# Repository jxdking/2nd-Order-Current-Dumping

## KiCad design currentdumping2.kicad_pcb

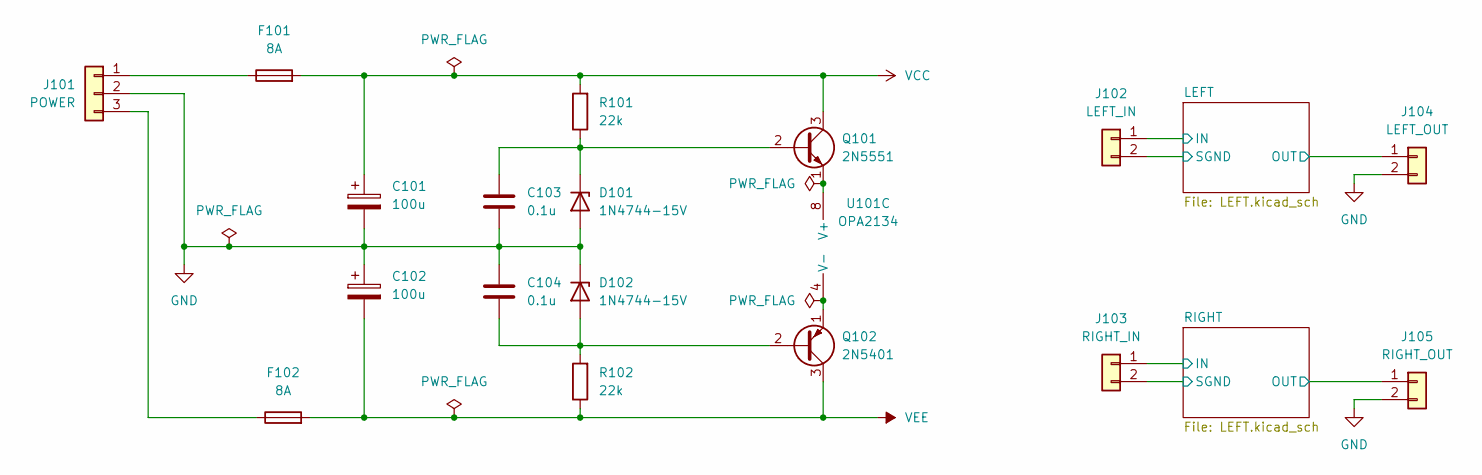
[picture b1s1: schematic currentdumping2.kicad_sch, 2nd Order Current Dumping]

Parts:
C101, C102: 100u; CP_Radial_D10.0mm_P5.00mm
C103, C104: 0.1u; C_Disc_D4.7mm_W2.5mm_P5.00mm
D101, D102: 1N4744-15V; D_DO-41_SOD81_P10.16mm_Horizontal
F101, F102: 8A; Fuseholder_Clip-5x20mm_Littelfuse_521_Lateral_P17.00x5.00mm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
J101: POWER; TerminalBlock_MaiXu_MX126-5.0-03P_1x03_P5.00mm
J102: LEFT_IN; TerminalBlock_MaiXu_MX126-5.0-02P_1x02_P5.00mm
J103: RIGHT_IN; TerminalBlock_MaiXu_MX126-5.0-02P_1x02_P5.00mm
J104: LEFT_OUT; TerminalBlock_MaiXu_MX126-5.0-02P_1x02_P5.00mm
J105: RIGHT_OUT; TerminalBlock_MaiXu_MX126-5.0-02P_1x02_P5.00mm
Q101: 2N5551; TO-92_Inline_Wide
Q102: 2N5401; TO-92_Inline_Wide
R101, R102: 22k; R_Axial_DIN0207_L6.3mm_D2.5mm_P10.16mm_Horizontal
U101: OPA2134; DIP-8_W7.62mm_Socket

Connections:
/LEFT/IN: J102.1; also elsewhere on the board
/LEFT/OUT: J104.1; also elsewhere on the board
/LEFT/SGND: J102.2; also elsewhere on the board
/RIGHT/IN: J103.1; also elsewhere on the board
/RIGHT/OUT: J105.1; also elsewhere on the board
/RIGHT/SGND: J103.2; also elsewhere on the board
GND: C101.2, C102.1, C103.2, C104.1, D101.2 (A), D102.1 (K), J101.2, J104.2, J105.2; also elsewhere on the board
unnamed: C103.1, D101.1 (K), Q101.2 (B), R101.1
unnamed: C104.2, D102.2 (A), Q102.2 (B), R102.2
unnamed: F101.1, J101.1
unnamed: F102.1, J101.3
unnamed: Q101.1 (E), U101.8 (V+)
unnamed: Q102.1 (E), U101.4 (V-)
unnamed 60: U101.7; also elsewhere on the board
unnamed 63: U101.5 (+); also elsewhere on the board
unnamed 64: U101.6 (-); also elsewhere on the board
VCC: C101.1, F101.2, Q101.3 (C), R101.2; also elsewhere on the board
VEE: C102.2, F102.2, Q102.3 (C), R102.1; also elsewhere on the board

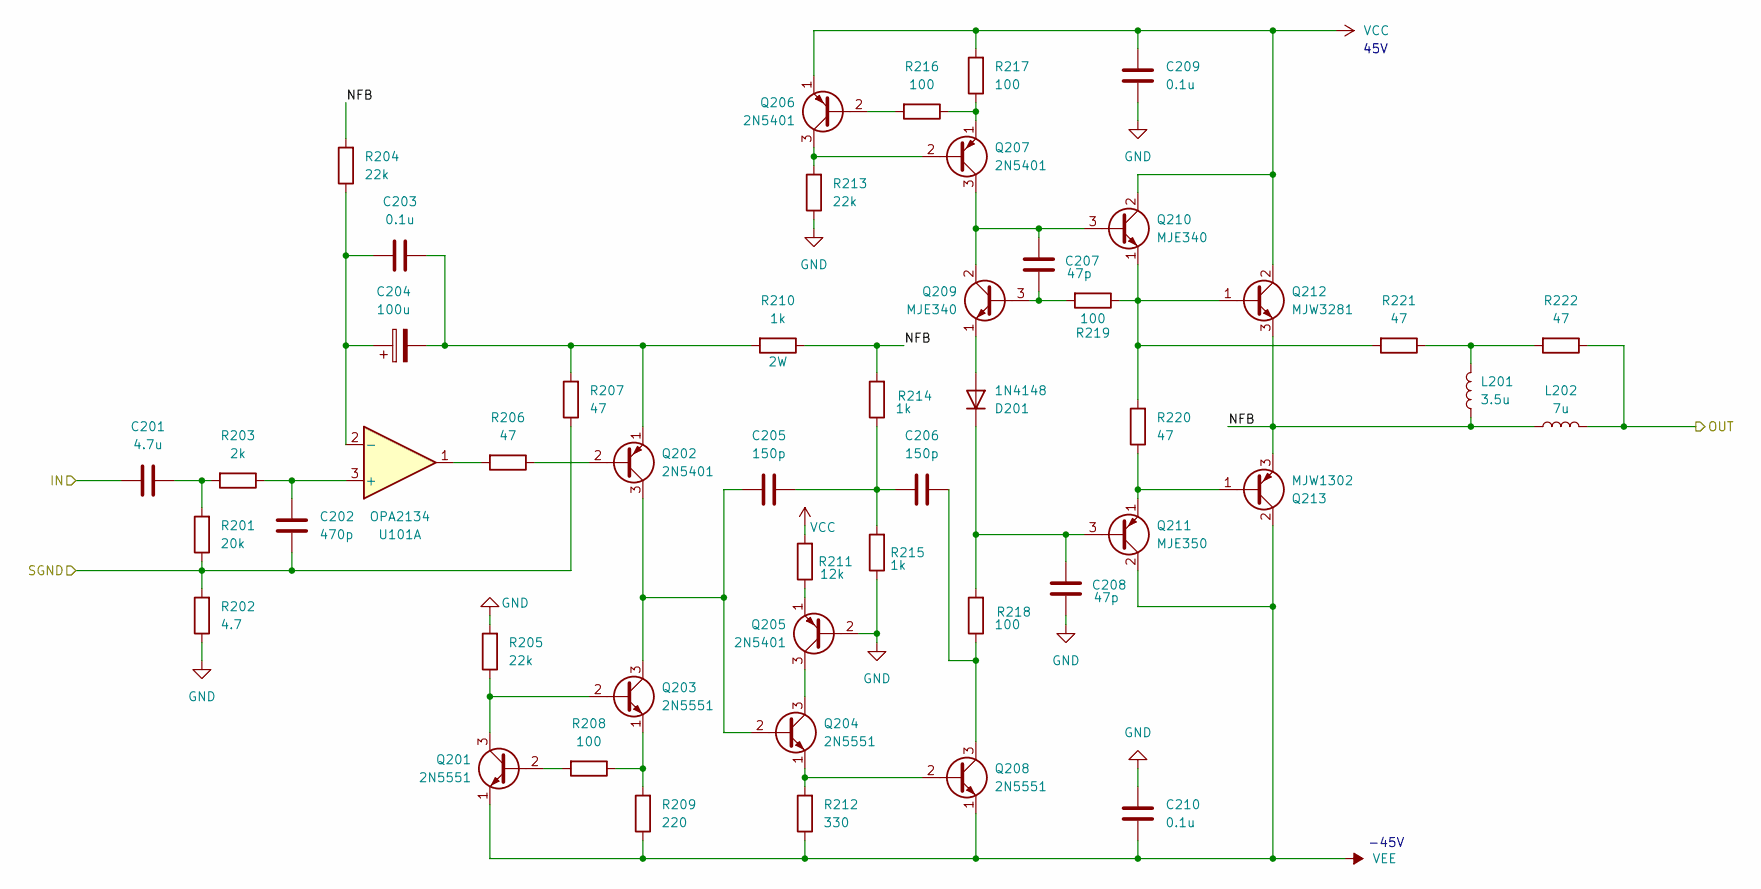
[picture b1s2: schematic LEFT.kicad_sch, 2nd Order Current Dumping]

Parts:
C201: 4.7u; C_Disc_D4.7mm_W2.5mm_P5.00mm
C202: 470p; C_Disc_D4.7mm_W2.5mm_P5.00mm
C203, C209, C210: 0.1u; C_Disc_D4.7mm_W2.5mm_P5.00mm
C204: 100u; CP_Radial_D5.0mm_P2.50mm
C205, C206: 150p; C_Disc_D4.7mm_W2.5mm_P5.00mm
C207, C208: 47p; C_Disc_D4.7mm_W2.5mm_P5.00mm
D201: 1N4148; D_DO-35_SOD27_P10.16mm_Horizontal
L201: 3.5u; L_Axial_L20.3mm_D12.7mm_P25.40mm_Horizontal_Vishay_IHA-201
L202: 7u; L_Axial_L20.3mm_D12.7mm_P25.40mm_Horizontal_Vishay_IHA-201
Q201, Q203, Q204, Q208: 2N5551; TO-92_Inline_Wide
Q202, Q205, Q206, Q207: 2N5401; TO-92_Inline_Wide
Q209, Q210: MJE340; TO-126-3_Horizontal_TabDown
Q211: MJE350; TO-126-3_Horizontal_TabDown
Q212: MJW3281; TO-247-3_Vertical
Q213: MJW1302; TO-247-3_Vertical
R201: 20k; R_Axial_DIN0207_L6.3mm_D2.5mm_P10.16mm_Horizontal
R202: 4.7; R_Axial_DIN0207_L6.3mm_D2.5mm_P10.16mm_Horizontal
R203: 2k; R_Axial_DIN0207_L6.3mm_D2.5mm_P10.16mm_Horizontal
R204, R205, R213: 22k; R_Axial_DIN0207_L6.3mm_D2.5mm_P10.16mm_Horizontal
R206, R207, R220, R221, R222: 47; R_Axial_DIN0207_L6.3mm_D2.5mm_P10.16mm_Horizontal
R208, R216, R217, R218, R219: 100; R_Axial_DIN0207_L6.3mm_D2.5mm_P10.16mm_Horizontal
R209: 220; R_Axial_DIN0207_L6.3mm_D2.5mm_P10.16mm_Horizontal
R210: 1k; R_Axial_DIN0414_L11.9mm_D4.5mm_P20.32mm_Horizontal
R211: 12k; R_Axial_DIN0207_L6.3mm_D2.5mm_P10.16mm_Horizontal
R212: 330; R_Axial_DIN0207_L6.3mm_D2.5mm_P10.16mm_Horizontal
R214, R215: 1k; R_Axial_DIN0207_L6.3mm_D2.5mm_P10.16mm_Horizontal
U101: OPA2134; DIP-8_W7.62mm_Socket

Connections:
/LEFT/IN: C201.1; also elsewhere on the board
/LEFT/NFB: L201.1, L202.1, Q212.3 (E), Q213.3 (E), R204.2, R210.1, R214.2
/LEFT/OUT: L202.2, R222.1; also elsewhere on the board
/LEFT/SGND: C202.1, R201.1, R202.2, R207.1; also elsewhere on the board
GND: C208.2, C209.2, C210.1, Q205.2 (B), R202.1, R205.2, R213.1, R215.1; also elsewhere on the board
unnamed: C201.2, R201.2, R203.2
unnamed: C205.2, C206.1, R214.1, R215.2
unnamed: D201.2 (A), Q209.1 (E)
unnamed: C208.1, D201.1 (K), Q211.3 (B), R218.2
unnamed: L201.2, R221.1, R222.2
unnamed: Q201.2 (B), R208.2
unnamed: Q201.3 (C), Q203.2 (B), R205.1
unnamed: Q202.2 (B), R206.1
unnamed: C205.1, Q202.3 (C), Q203.3 (C), Q204.2 (B)
unnamed: C203.2, C204.2, Q202.1 (E), R207.2, R210.2
unnamed: Q203.1 (E), R208.1, R209.2
unnamed: Q204.3 (C), Q205.3 (C)
unnamed: Q204.1 (E), Q208.2 (B), R212.2
unnamed: Q205.1 (E), R211.1
unnamed: Q206.2 (B), R216.2
unnamed: Q206.3 (C), Q207.2 (B), R213.2
unnamed: C207.1, Q207.3 (C), Q209.2 (C), Q210.3 (B)
unnamed: Q207.1 (E), R216.1, R217.1
unnamed: C206.2, Q208.3 (C), R218.1
unnamed: C207.2, Q209.3 (B), R219.2
unnamed: Q210.1 (E), Q212.1 (B), R219.1, R220.2, R221.2
unnamed: Q211.1 (E), Q213.1 (B), R220.1
unnamed: R206.2, U101.1
unnamed 60: U101.7; also elsewhere on the board
unnamed: C202.2, R203.1, U101.3 (+)
unnamed: C203.1, C204.1, R204.1, U101.2 (-)
unnamed 63: U101.5 (+); also elsewhere on the board
unnamed 64: U101.6 (-); also elsewhere on the board
VCC: C209.1, Q206.1 (E), Q210.2 (C), Q212.2 (C), R211.2, R217.2; also elsewhere on the board
VEE: C210.2, Q201.1 (E), Q208.1 (E), Q211.2 (C), Q213.2 (C), R209.1, R212.1; also elsewhere on the board

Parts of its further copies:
C301: 4.7u; C_Disc_D4.7mm_W2.5mm_P5.00mm
C302: 470p; C_Disc_D4.7mm_W2.5mm_P5.00mm
C303, C309, C310: 0.1u; C_Disc_D4.7mm_W2.5mm_P5.00mm
C304: 100u; CP_Radial_D5.0mm_P2.50mm
C305, C306: 150p; C_Disc_D4.7mm_W2.5mm_P5.00mm
C307, C308: 47p; C_Disc_D4.7mm_W2.5mm_P5.00mm
D301: 1N4148; D_DO-35_SOD27_P10.16mm_Horizontal
L301: 3.5u; L_Axial_L20.3mm_D12.7mm_P25.40mm_Horizontal_Vishay_IHA-201
L302: 7u; L_Axial_L20.3mm_D12.7mm_P25.40mm_Horizontal_Vishay_IHA-201
Q301, Q303, Q304, Q308: 2N5551; TO-92_Inline_Wide
Q302, Q305, Q306, Q307: 2N5401; TO-92_Inline_Wide
Q309, Q310: MJE340; TO-126-3_Horizontal_TabDown
Q311: MJE350; TO-126-3_Horizontal_TabDown
Q312: MJW3281; TO-247-3_Vertical
Q313: MJW1302; TO-247-3_Vertical
R301: 20k; R_Axial_DIN0207_L6.3mm_D2.5mm_P10.16mm_Horizontal
R302: 4.7; R_Axial_DIN0207_L6.3mm_D2.5mm_P10.16mm_Horizontal
R303: 2k; R_Axial_DIN0207_L6.3mm_D2.5mm_P10.16mm_Horizontal
R304, R305, R313: 22k; R_Axial_DIN0207_L6.3mm_D2.5mm_P10.16mm_Horizontal
R306, R307, R320, R321, R322: 47; R_Axial_DIN0207_L6.3mm_D2.5mm_P10.16mm_Horizontal
R308, R316, R317, R318, R319: 100; R_Axial_DIN0207_L6.3mm_D2.5mm_P10.16mm_Horizontal
R309: 220; R_Axial_DIN0207_L6.3mm_D2.5mm_P10.16mm_Horizontal
R310: 1k; R_Axial_DIN0414_L11.9mm_D4.5mm_P20.32mm_Horizontal
R311: 12k; R_Axial_DIN0207_L6.3mm_D2.5mm_P10.16mm_Horizontal
R312: 330; R_Axial_DIN0207_L6.3mm_D2.5mm_P10.16mm_Horizontal
R314, R315: 1k; R_Axial_DIN0207_L6.3mm_D2.5mm_P10.16mm_Horizontal

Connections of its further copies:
/RIGHT/IN: C301.1; also elsewhere on the board
/RIGHT/NFB: L301.1, L302.1, Q312.3 (E), Q313.3 (E), R304.2, R310.1, R314.2
/RIGHT/OUT: L302.2, R322.1; also elsewhere on the board
/RIGHT/SGND: C302.1, R301.1, R302.2, R307.1; also elsewhere on the board
GND: C308.2, C309.2, C310.1, Q305.2 (B), R302.1, R305.2, R313.1, R315.1; also elsewhere on the board
unnamed: C301.2, R301.2, R303.2
unnamed: C305.2, C306.1, R314.1, R315.2
unnamed: D301.2 (A), Q309.1 (E)
unnamed: C308.1, D301.1 (K), Q311.3 (B), R318.2
unnamed: L301.2, R321.1, R322.2
unnamed: Q301.2 (B), R308.2
unnamed: Q301.3 (C), Q303.2 (B), R305.1
unnamed: Q302.2 (B), R306.1
unnamed: C305.1, Q302.3 (C), Q303.3 (C), Q304.2 (B)
unnamed: C303.2, C304.2, Q302.1 (E), R307.2, R310.2
unnamed: Q303.1 (E), R308.1, R309.2
unnamed: Q304.3 (C), Q305.3 (C)
unnamed: Q304.1 (E), Q308.2 (B), R312.2
unnamed: Q305.1 (E), R311.1
unnamed: Q306.2 (B), R316.2
unnamed: Q306.3 (C), Q307.2 (B), R313.2
unnamed: C307.1, Q307.3 (C), Q309.2 (C), Q310.3 (B)
unnamed: Q307.1 (E), R316.1, R317.1
unnamed: C306.2, Q308.3 (C), R318.1
unnamed: C307.2, Q309.3 (B), R319.2
unnamed: Q310.1 (E), Q312.1 (B), R319.1, R320.2, R321.2
unnamed: Q311.1 (E), Q313.1 (B), R320.1
unnamed 60: R306.2; also elsewhere on the board
unnamed 63: C302.2, R303.1; also elsewhere on the board
unnamed 64: C303.1, C304.1, R304.1; also elsewhere on the board
VCC: C309.1, Q306.1 (E), Q310.2 (C), Q312.2 (C), R311.2, R317.2; also elsewhere on the board
VEE: C310.2, Q301.1 (E), Q308.1 (E), Q311.2 (C), Q313.2 (C), R309.1, R312.1; also elsewhere on the board

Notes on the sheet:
45V
-45V

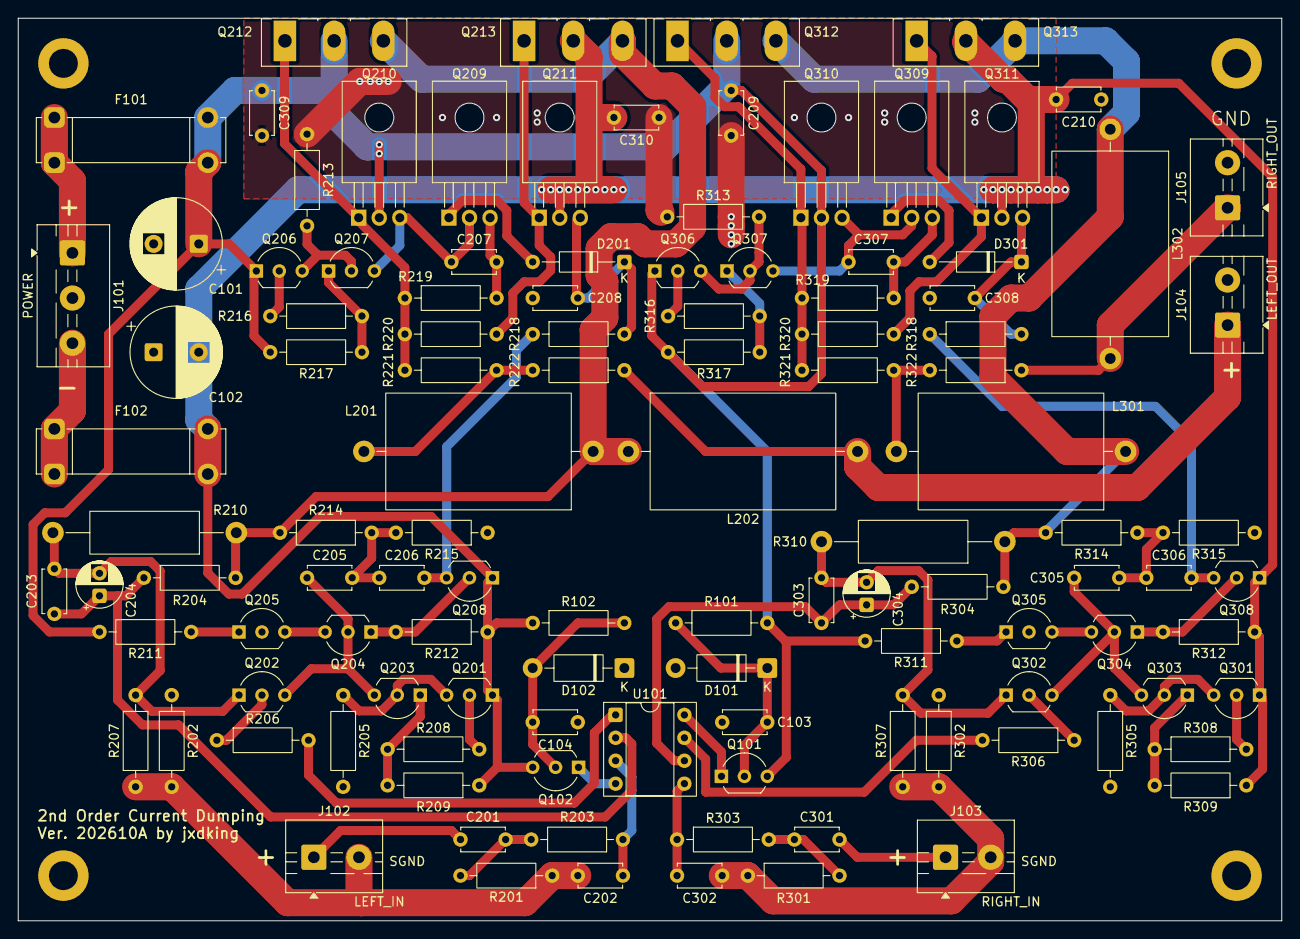
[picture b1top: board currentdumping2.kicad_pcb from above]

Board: 2 copper layers, 140.0 x 100.0 mm, 114 parts (0 on the bottom side), 67 nets.
